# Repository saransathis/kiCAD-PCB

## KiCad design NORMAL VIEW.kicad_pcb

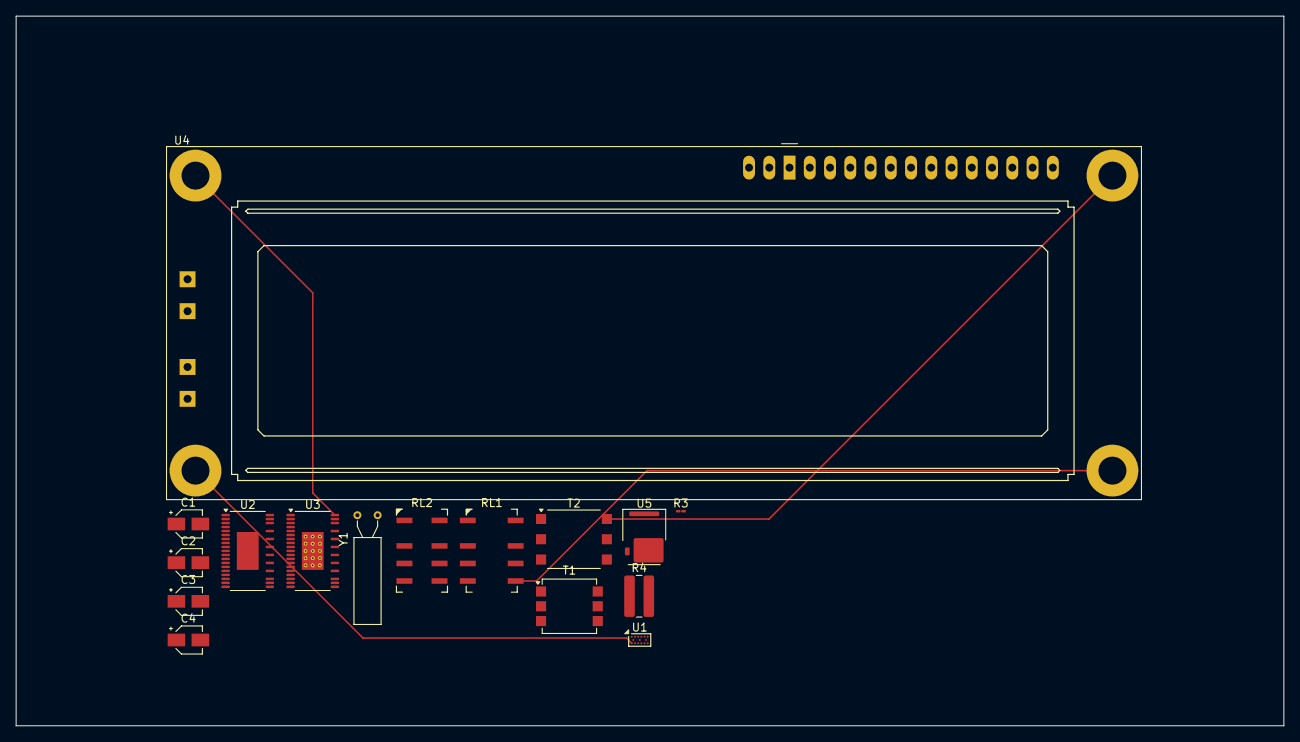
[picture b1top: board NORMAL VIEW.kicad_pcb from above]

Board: 2 copper layers, 159.0 x 89.0 mm, 16 parts (0 on the bottom side), 13 nets.

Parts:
C1, C2, C3, C4: C_Small; CP_Elec_3x5.3
R3: R; R_01005_0402Metric_Pad0.57x0.30mm_HandSolder
R4: R; R_1020_2550Metric_Pad1.33x5.20mm_HandSolder
RL1: AZSR131-1AE-12D; Relay_2P2T_10x6mm_TE_IMxxG
RL2: AZSR131-1AE-12D; Relay_DPDT_AXICOM_IMSeries_JLeg
T1: Transformer_1P_1S; Pulse_P0926NL
T2: Transformer_1P_1S; Pulse_PA1323NL
U1: PIC16F877A-IP; Nexperia_WLCSP-15_2.37x1.17mm_Layout6x3_P0.4mmP0.8mm
U2: LM358; Linear_HTSSOP-31-38-1EP_4.4x9.7mm_P0.5mm_EP2.74x4.75mm
U3: LM358; Linear_HTSSOP-31-38-1EP_4.4x9.7mm_P0.5mm_EP2.74x4.75mm_Ther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
U4: LCD-016N002L
U5: ULN2002A; GaN_Systems_GaNPX-3_5x6.6mm_Drain3.76x0.6mm
Y1: Crystal; Crystal_AT310_D3.0mm_L10.0mm_Horizontal

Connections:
Earth: U2.4 (V-), U3.4 (V-)
unnamed: C1.1, Y1.2
unnamed: C2.2, Y1.1
unnamed: C3.2, RL1.2
unnamed: C4.2, RL2.4
unnamed: RL1.3, RL2.2
unnamed: T1.1 (AA), U3.2 (-)
unnamed: R4.1, T1.2 (AB)
unnamed: T2.1 (AA), U2.6 (-)
unnamed: R3.1, T2.2 (AB)
unnamed: R3.2, U2.5 (+)
unnamed: R4.2, U3.3 (+)
VCC: U2.8 (V+), U3.8 (V+)

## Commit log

2025-03-30 PCD DESIGN
